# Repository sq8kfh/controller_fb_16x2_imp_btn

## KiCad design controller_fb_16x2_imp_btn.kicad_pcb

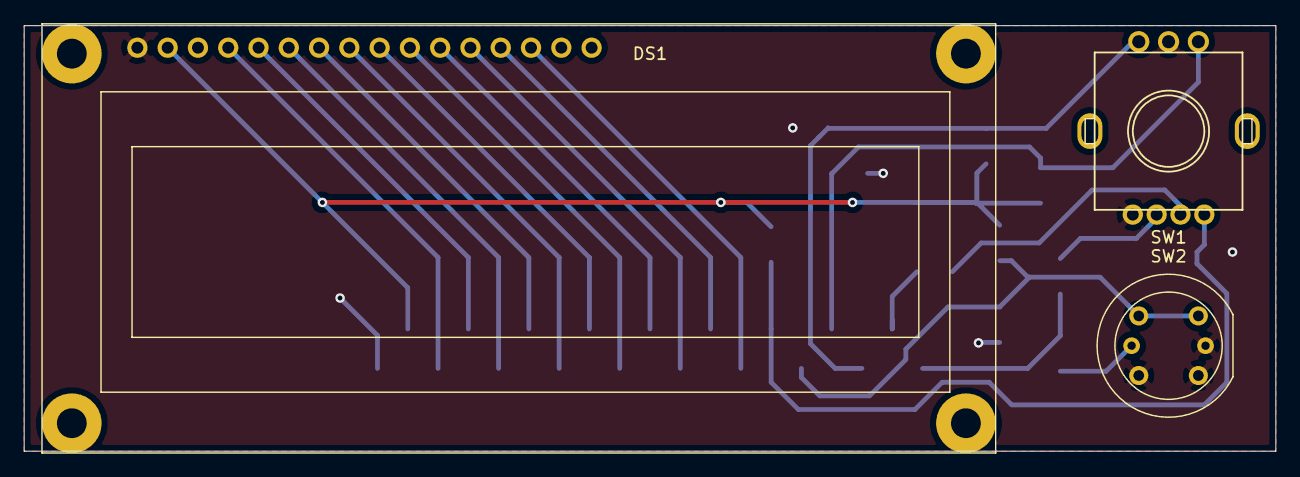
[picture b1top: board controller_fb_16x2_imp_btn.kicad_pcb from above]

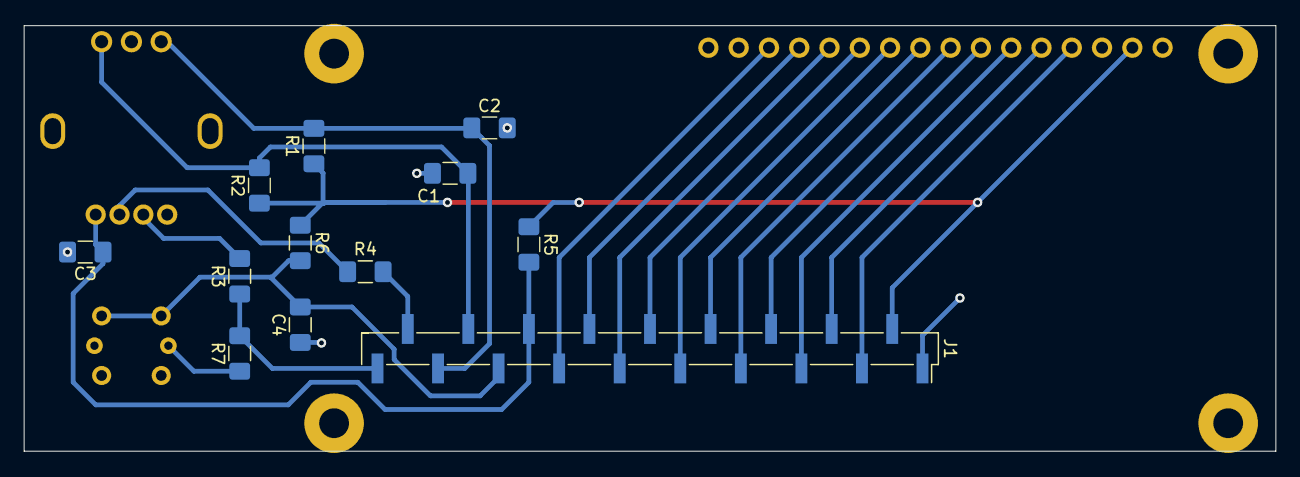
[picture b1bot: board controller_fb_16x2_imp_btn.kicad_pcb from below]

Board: 2 copper layers, 105.0 x 35.7 mm, 15 parts (12 on the bottom side), 22 nets.

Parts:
C1, C2, C3, C4: 100nF; C_1206_3216Metric_Pad1.42x1.75mm_HandSolder
DS1: RS0010; REC001602A
J1: Conn_01x19; PinHeader_1x19_P2.54mm_Vertical_SMD_Pin1Right
R1, R2, R5, R6: 10k; R_1206_3216Metric_Pad1.42x1.75mm_HandSolder
R3, R4, R7: 470R; R_1206_3216Metric_Pad1.42x1.75mm_HandSolder
SW1: Rotary_Encoder_with_Dual_LED_and_Switch; PEL12D-4xxxS-Sxxxx
SW2: SW_Push_LED; SW_PUSH_HIGHLY_KS01-BL

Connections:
+5V: DS1.2, J1.2, R1.1, R2.1, R5.1, R6.1
/PB0(MISO): DS1.4, J1.3
/PB1(MOSI): DS1.5, J1.4
/PB2(INT1): DS1.10, J1.9
/PB3: C3.1, J1.14, R5.2, SW1.4
/PB4: C4.2, J1.15, R6.2, SW2.2
/PB5(INT2): C1.1, J1.16, R2.2, SW1.A
/PB6: C2.1, J1.17, R1.2, SW1.B
/PB7(SCK): DS1.6, J1.5
/PC0(INT3): J1.19, R3.1, R7.2
/PC4: DS1.11, J1.10
/PC5: DS1.12, J1.11
/PC6: DS1.13, J1.12
/PC7(D2A): DS1.14, J1.13
/PD0: J1.18, R4.1
/PD5: DS1.7, J1.6
/PD6: DS1.8, J1.7
/PD7: DS1.9, J1.8
GND: C1.2, C2.2, C3.2, C4.1, DS1.1, J1.1, SW1.1, SW1.C, SW2.1, SW2.3
unnamed: R3.2, SW1.2
unnamed: R4.2, SW1.3
unnamed: R7.1, SW2.4

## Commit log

2020-12-23 Init v0.1
2020-12-24 Add production files
